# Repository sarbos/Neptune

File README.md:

#Neptune

Open source software and hardware for inexpensive Underwater ROV

device - all code on the ROV side of the project. Includes sensor drivers, motor drivers, HTTP communication, etc.

host - python host code to communicate with the device over http. Provides UI for controlling and viewing cameras and main board. Also interprets USB joystick and gamepad controls.

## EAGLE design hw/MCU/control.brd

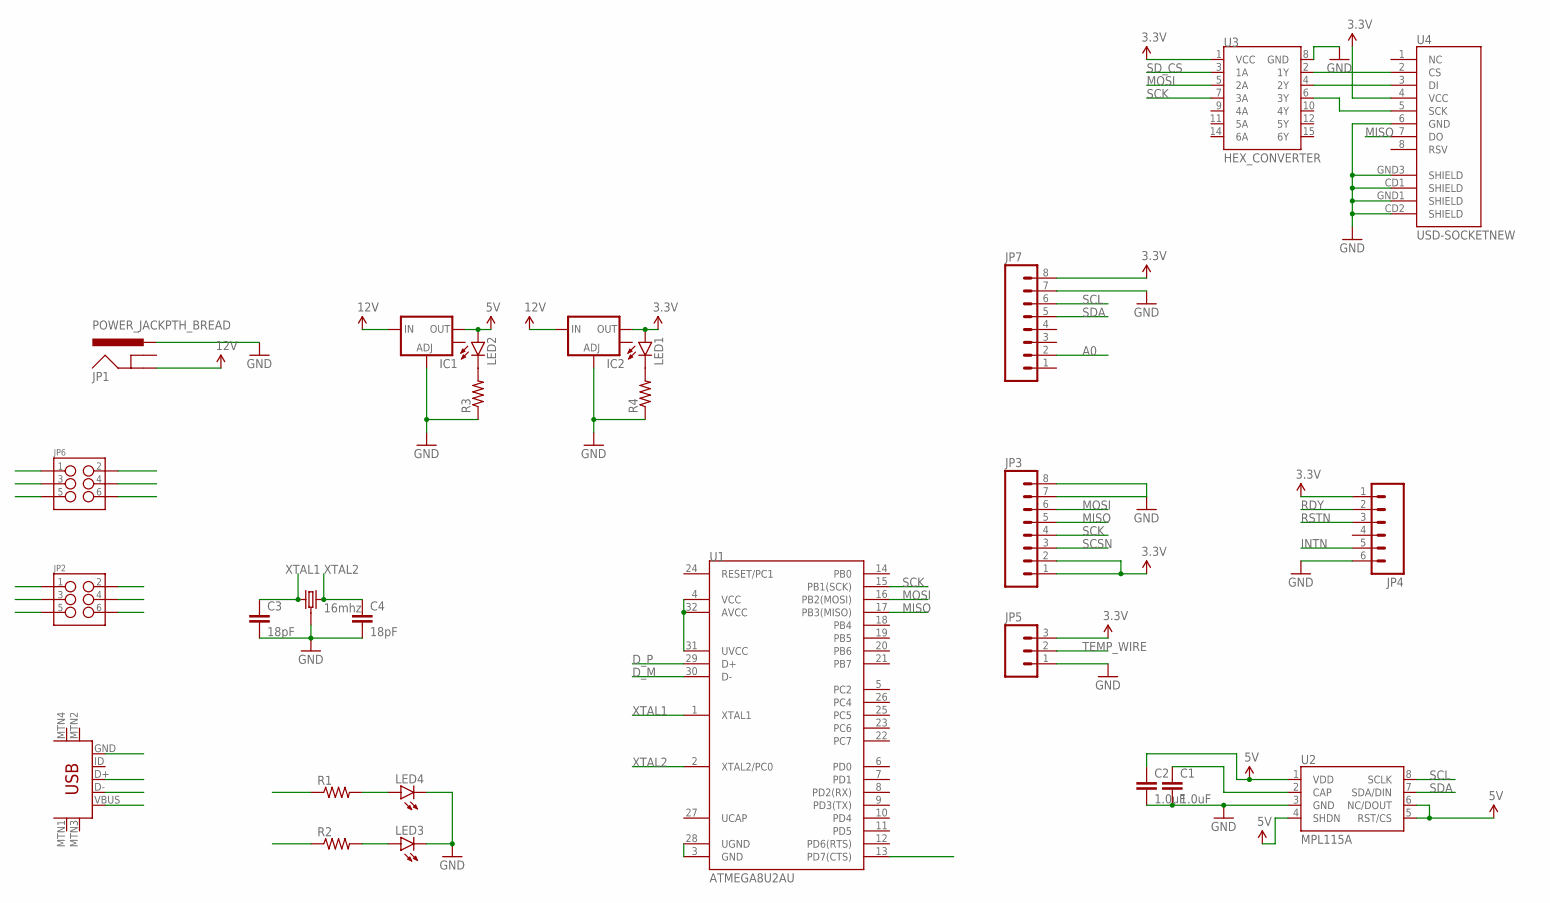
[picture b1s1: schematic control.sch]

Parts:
C1, C2: 1.0uF; 0603-CAP
C3, C4: 18pF; 0603-CAP
IC1, IC2: V_REG_LM1117SOT223; SOT223
JP1: POWER_JACKPTH_BREAD; POWER_JACK_PTH_BREAD
JP2, JP6: M03X2SHROUD; 2X3-SHROUDED
JP3, JP7: M08; 1X08_ROUND
JP4: M06SILK_FEMALE_PTH; 1X06
JP5: M03PTH; 1X03
LED1, LED2, LED3, LED4: LED0603; LED-0603
R1, R2, R3, R4: RESISTOR0603-RES; 0603-RES
U1: ATMEGA8U2AU; TQFP32-08
U2: MPL115A; LGA8
U3: HEX_CONVERTER; SO016
U4: USD-SOCKETNEW; MICRO-SD-SOCKET-PP
U$3: 16mhz; CRYSTAL-SMD-5X3
U$5: USB-MINIB-5PIN; USB-MINIB

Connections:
3.3V: IC2.2 (OUT), JP3.1, JP3.2, JP4.1, JP5.3, JP7.8, LED1.A, U3.1 (VCC), U4.4 (VCC)
5V: C2.1, IC1.2 (OUT), LED2.A, U2.1 (VDD), U2.4 (SHDN), U2.5 (RST/CS), U2.6 (NC/DOUT)
12V: IC1.3 (IN), IC2.3 (IN), JP1.GND
A0: JP7.2
D_M: U1.30 (D-)
D_P: U1.29 (D+)
GND: C1.2, C2.2, C3.2, C4.2, IC1.1 (ADJ), IC2.1 (ADJ), JP1.PWR, JP4.6, JP5.1, JP7.7, LED3.C, LED4.C, R3.1, R4.1, U2.3 (GND), U3.8 (GND), U4.6 (GND), U4.CD1 (SHIELD), U4.CD2 (SHIELD), U4.GND1 (SHIELD), U4.GND3 (SHIELD), U$3.2 (3), U$3.4 (3)
INTN: JP4.5
MISO: JP3.5, U1.17 (PB3(MISO)), U4.7 (DO)
MOSI: JP3.6, U1.16 (PB2(MOSI)), U3.5 (2A)
unnamed: JP3.7, JP3.8
unnamed: LED4.A, R1.2
unnamed: LED3.A, R2.2
unnamed: LED2.C, R3.2
unnamed: LED1.C, R4.2
unnamed: U3.2 (1Y), U4.2 (CS)
unnamed: U3.4 (2Y), U4.3 (DI)
unnamed: U3.6 (3Y), U4.5 (SCK)
unnamed: C1.1, U2.2 (CAP)
unnamed: U1.3 (GND), U1.28 (UGND)
unnamed: U1.4 (VCC), U1.31 (UVCC), U1.32 (AVCC)
RDY: JP4.2
RSTN: JP4.3
SCK: JP3.4, U1.15 (PB1(SCK)), U3.7 (3A)
SCL: JP7.6, U2.8 (SCLK)
SCSN: JP3.3
SDA: JP7.5, U2.7 (SDA/DIN)
SD_CS: U3.3 (1A)
TEMP_WIRE: JP5.2
XTAL1: C3.1, U1.1 (XTAL1), U$3.3 (1)
XTAL2: C4.1, U1.2 (XTAL2/PC0), U$3.1 (2)

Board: 2 copper layers, 27 parts (1 on the bottom side), 22 nets, no tracks yet.

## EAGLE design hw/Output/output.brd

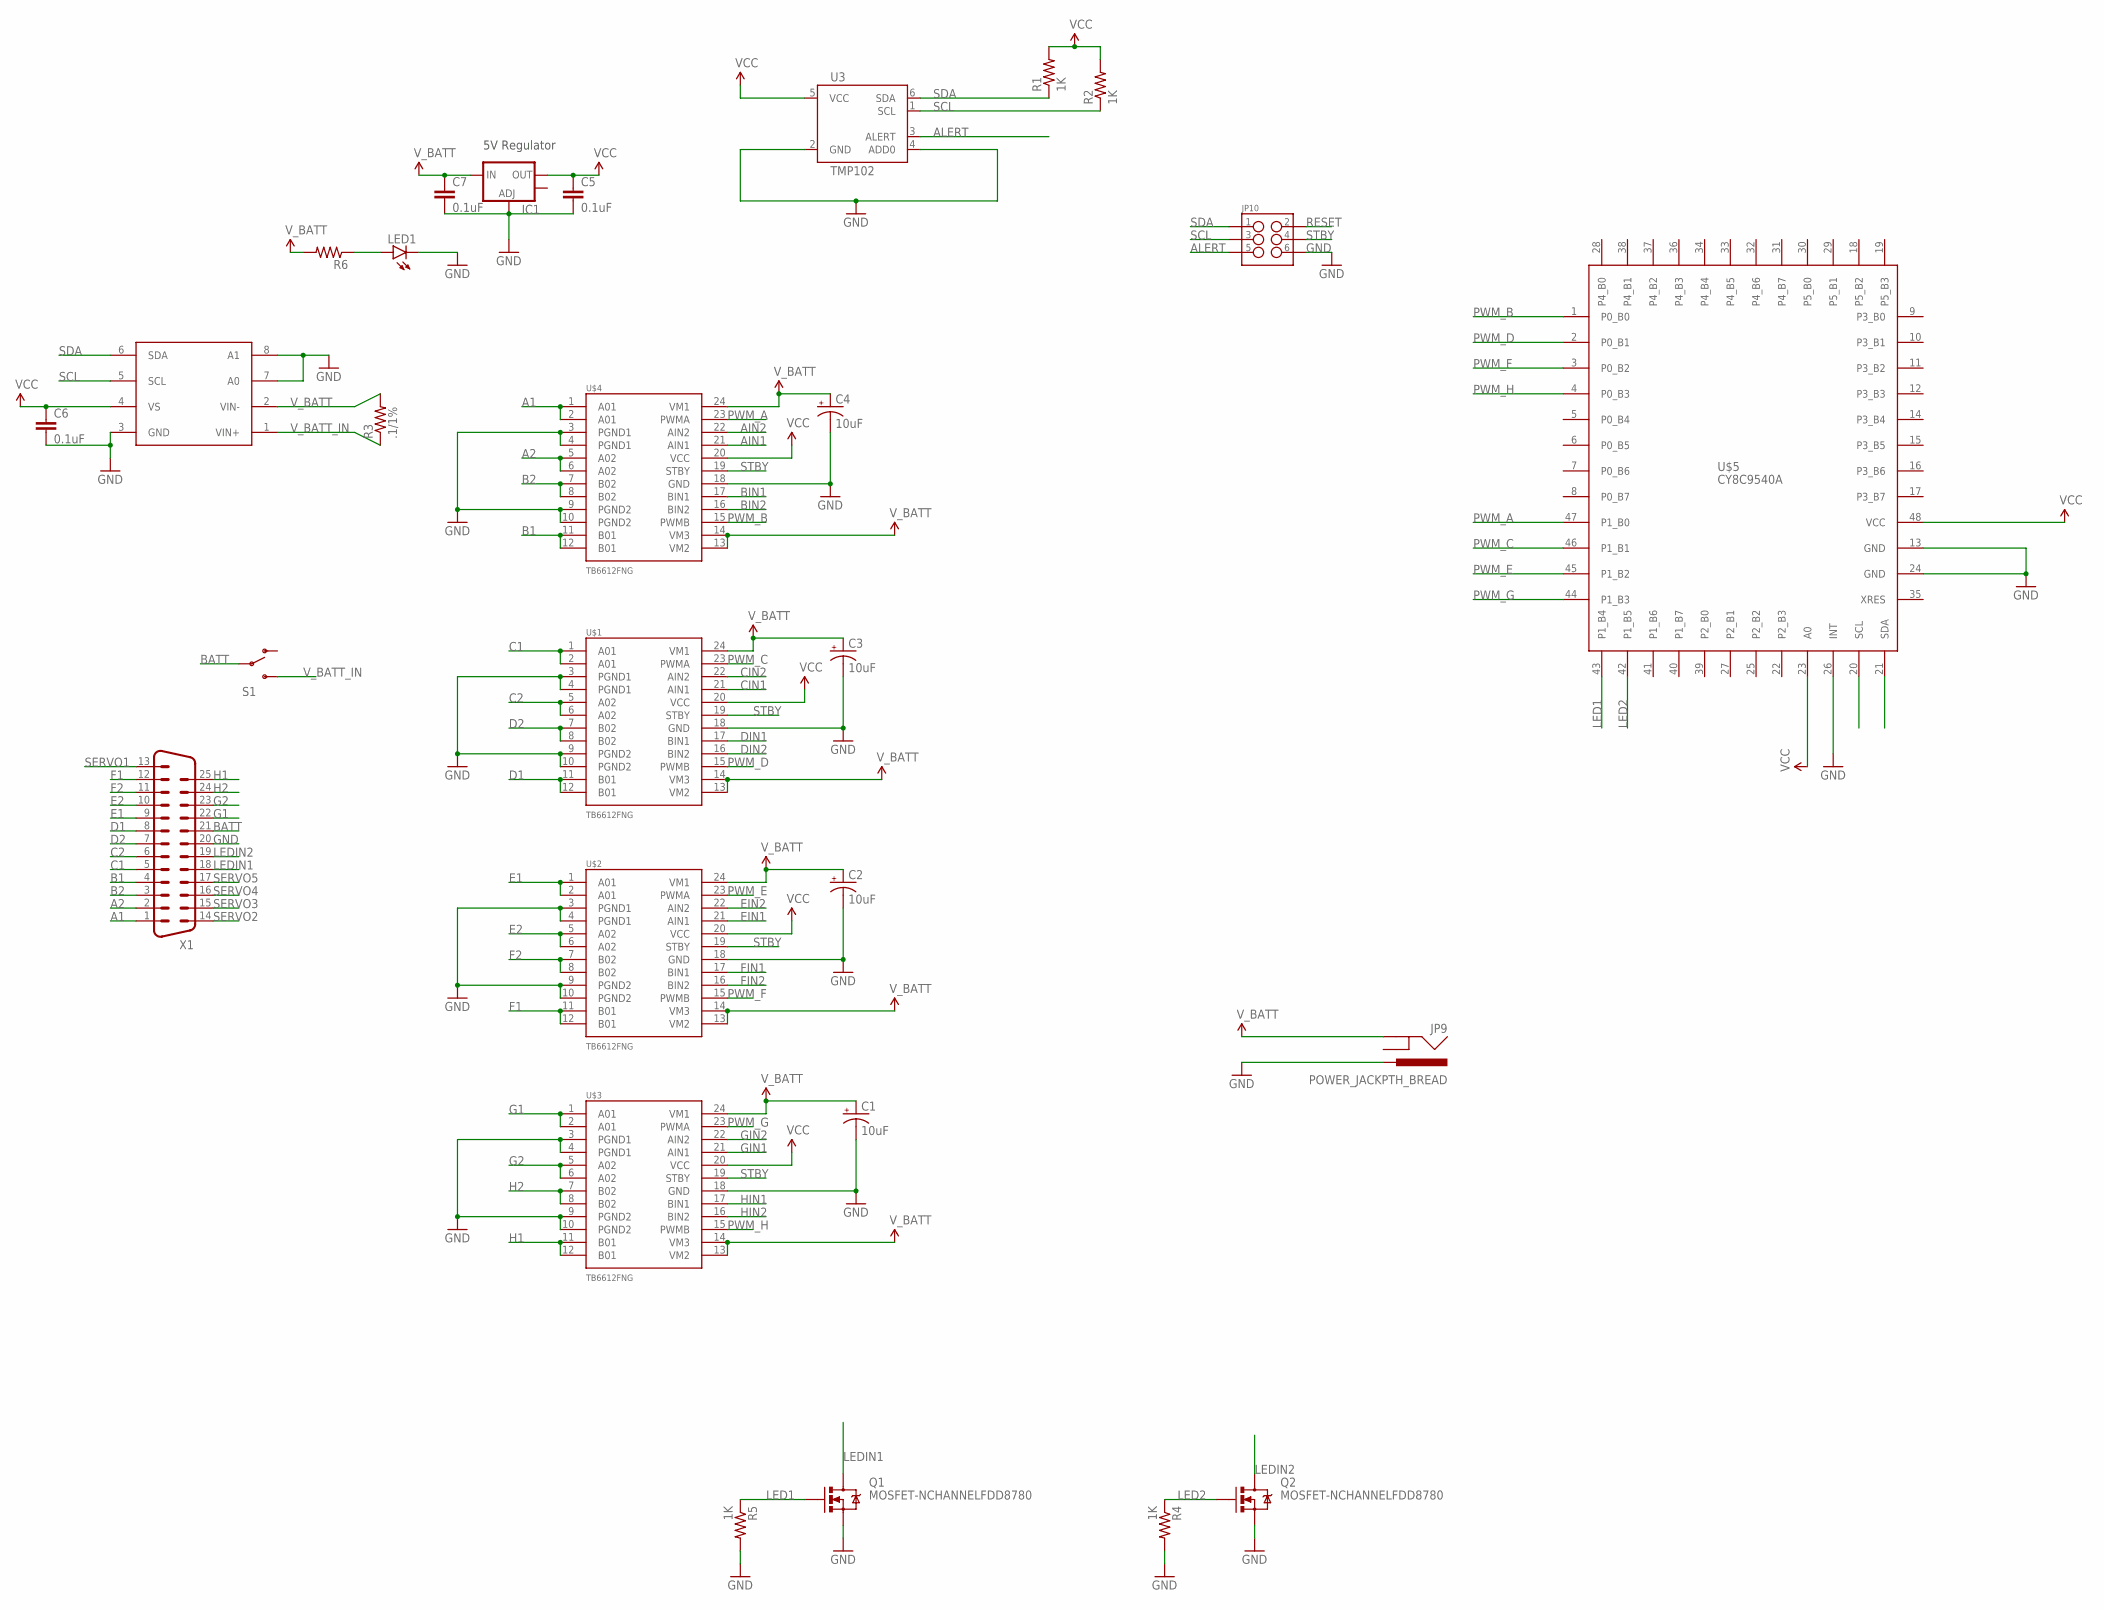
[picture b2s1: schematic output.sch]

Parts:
C1, C2, C3, C4: 10uF; EIA3528
C5, C6, C7: 0.1uF; 0603-CAP
IC1: V_REG_LM1117SOT223; SOT223
JP9: POWER_JACKPTH_BREAD; POWER_JACK_PTH_BREAD
JP10: M03X2SHROUD; 2X3-SHROUDED
LED1: LED0603; LED-0603
Q1, Q2: MOSFET-NCHANNELFDD8780; DPAK
R1, R2, R4, R5: 1K; 0603-RES
R3: .1/1%; R2512
R6: RESISTOR0603-RES; 0603-RES
S1: SWITCH-SPDTKIT; SWITCH-SPDT_KIT
U3: TMP102; SOT563
U$1, U$2, U$3, U$4: TB6612FNG; SSOP24
U$5: CY8C9540A; 48-SSOP-CY
U$6: INA219; SOT23-8
X1: DB25D; M25D

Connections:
A1: U$4.1 (A01), U$4.2 (A01), X1.1
A2: U$4.5 (A02), U$4.6 (A02), X1.2
AIN1: U$4.21 (AIN1)
AIN2: U$4.22 (AIN2)
ALERT: JP10.5, U3.3 (ALERT)
B1: U$4.11 (B01), U$4.12 (B01), X1.4
B2: U$4.7 (B02), U$4.8 (B02), X1.3
BATT: S1.2, X1.21
BIN1: U$4.17 (BIN1)
BIN2: U$4.16 (BIN2)
C1: U$1.1 (A01), U$1.2 (A01), X1.5
C2: U$1.5 (A02), U$1.6 (A02), X1.6
CIN1: U$1.21 (AIN1)
CIN2: U$1.22 (AIN2)
D1: U$1.11 (B01), U$1.12 (B01), X1.8
D2: U$1.7 (B02), U$1.8 (B02), X1.7
DIN1: U$1.17 (BIN1)
DIN2: U$1.16 (BIN2)
E1: U$2.1 (A01), U$2.2 (A01), X1.9
E2: U$2.5 (A02), U$2.6 (A02), X1.10
EIN1: U$2.21 (AIN1)
EIN2: U$2.22 (AIN2)
F1: U$2.11 (B01), U$2.12 (B01), X1.12
F2: U$2.7 (B02), U$2.8 (B02), X1.11
FIN1: U$2.17 (BIN1)
FIN2: U$2.16 (BIN2)
G1: U$3.1 (A01), U$3.2 (A01), X1.22
G2: U$3.5 (A02), U$3.6 (A02), X1.23
GIN1: U$3.21 (AIN1)
GIN2: U$3.22 (AIN2)
GND: C1.C (-), C2.C (-), C3.C (-), C4.C (-), C5.2, C6.2, C7.2, IC1.1 (ADJ), JP9.PWR, JP10.6, LED1.C, Q1.3 (S), Q2.3 (S), R4.2, R5.2, U3.2 (GND), U3.4 (ADD0), U$1.3 (PGND1), U$1.4 (PGND1), U$1.9 (PGND2), U$1.10 (PGND2), U$1.18 (GND), U$2.3 (PGND1), U$2.4 (PGND1), U$2.9 (PGND2), U$2.10 (PGND2), U$2.18 (GND), U$3.3 (PGND1), U$3.4 (PGND1), U$3.9 (PGND2), U$3.10 (PGND2), U$3.18 (GND), U$4.3 (PGND1), U$4.4 (PGND1), U$4.9 (PGND2), U$4.10 (PGND2), U$4.18 (GND), U$5.13 (GND), U$5.24 (GND), U$5.26 (INT), U$6.3 (GND), U$6.7 (A0), U$6.8 (A1), X1.20
H1: U$3.11 (B01), U$3.12 (B01), X1.25
H2: U$3.7 (B02), U$3.8 (B02), X1.24
HIN1: U$3.17 (BIN1)
HIN2: U$3.16 (BIN2)
LED1: Q1.1 (G), R5.1, U$5.43 (P1_B4)
LED2: Q2.1 (G), R4.1, U$5.42 (P1_B5)
LEDIN1: Q1.4 (D), X1.18
LEDIN2: Q2.4 (D), X1.19
unnamed: LED1.A, R6.1
PWM_A: U$4.23 (PWMA), U$5.47 (P1_B0)
PWM_B: U$4.15 (PWMB), U$5.1 (P0_B0)
PWM_C: U$1.23 (PWMA), U$5.46 (P1_B1)
PWM_D: U$1.15 (PWMB), U$5.2 (P0_B1)
PWM_E: U$2.23 (PWMA), U$5.45 (P1_B2)
PWM_F: U$2.15 (PWMB), U$5.3 (P0_B2)
PWM_G: U$3.23 (PWMA), U$5.44 (P1_B3)
PWM_H: U$3.15 (PWMB), U$5.4 (P0_B3)
RESET: JP10.2
SCL: JP10.3, R2.1, U3.1 (SCL), U$5.20 (SCL), U$6.5 (SCL)
SDA: JP10.1, R1.1, U3.6 (SDA), U$5.21 (SDA), U$6.6 (SDA)
SERVO1: X1.13
SERVO2: X1.14
SERVO3: X1.15
SERVO4: X1.16
SERVO5: X1.17
STBY: JP10.4, U$1.19 (STBY), U$2.19 (STBY), U$3.19 (STBY), U$4.19 (STBY)
VCC: C5.1, C6.1, IC1.2 (OUT), R1.2, R2.2, U3.5 (VCC), U$1.20 (VCC), U$2.20 (VCC), U$3.20 (VCC), U$4.20 (VCC), U$5.23 (A0), U$5.48 (VCC), U$6.4 (VS)
V_BATT: C1.A (+), C2.A (+), C3.A (+), C4.A (+), C7.1, IC1.3 (IN), JP9.GND, R3.2, R6.2, U$1.13 (VM2), U$1.14 (VM3), U$1.24 (VM1), U$2.13 (VM2), U$2.14 (VM3), U$2.24 (VM1), U$3.13 (VM2), U$3.14 (VM3), U$3.24 (VM1), U$4.13 (VM2), U$4.14 (VM3), U$4.24 (VM1), U$6.2 (VIN-)
V_BATT_IN: R3.1, S1.3 (S), U$6.1 (VIN+)

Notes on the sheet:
5V Regulator

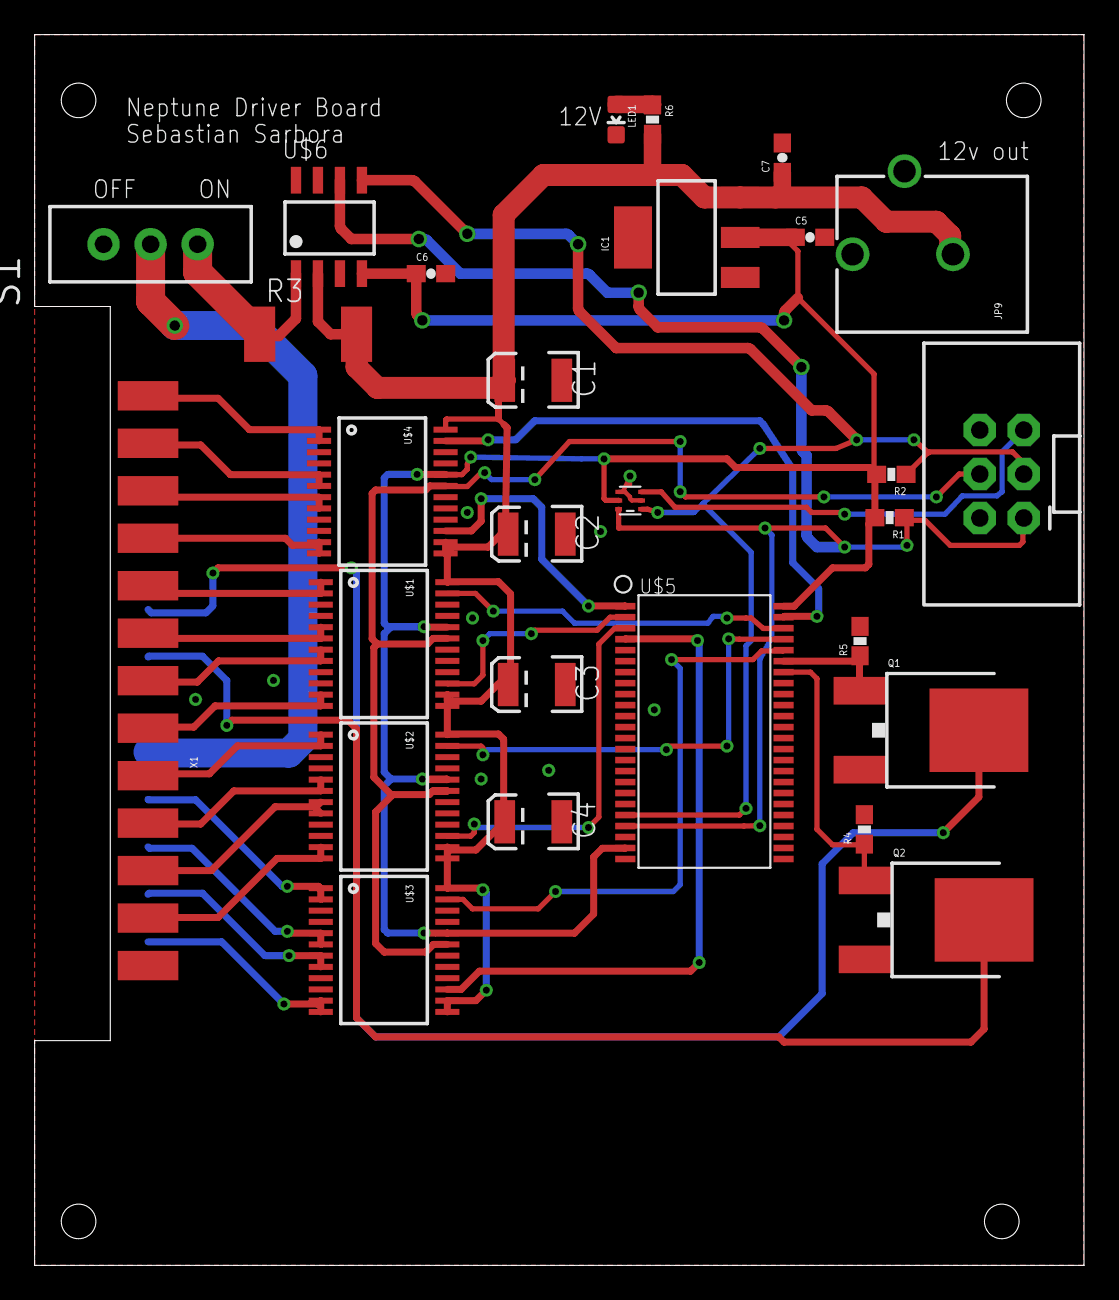
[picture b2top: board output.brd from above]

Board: 2 copper layers, 60.6 x 71.1 mm, 28 parts (0 on the bottom side), 38 nets.

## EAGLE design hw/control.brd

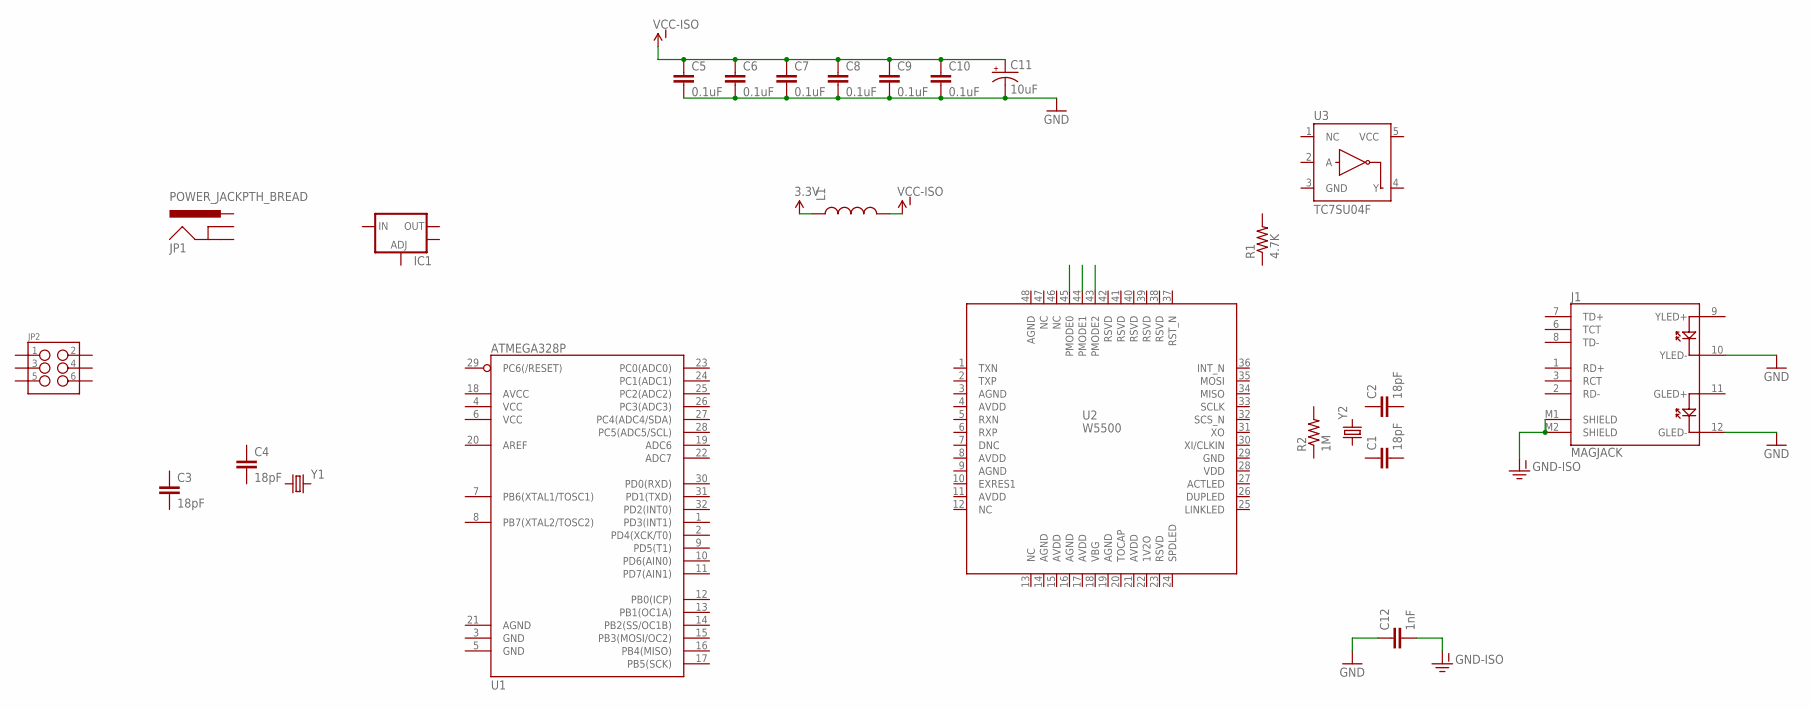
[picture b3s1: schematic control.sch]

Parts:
C1, C2, C3, C4: 18pF; 0603-CAP
C5, C6, C7, C8, C9, C10: 0.1uF; 0603-CAP
C11: 10uF; EIA3216
C12: 1nF; 0603-CAP
IC1: V_REG_LM1117SOT223; SOT223
J1: MAGJACK
JP1: POWER_JACKPTH_BREAD; POWER_JACK_PTH_BREAD
JP2: M03X2SHROUD; 2X3-SHROUDED
L1: INDUCTOR0603; 0603
R1: 4.7K; 0603-RES
R2: 1M; 0603-RES
U1: ATMEGA328P; TQFP32-08
U2: W5500
U3: TC7SU04F; SOT23-5
Y1, Y2: CRYSTALHC49US; HC49US

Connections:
3.3V: L1.1
GND: C5.2, C6.2, C7.2, C8.2, C9.2, C10.2, C11.C (-), C12.1, J1.10 (YLED-), J1.12 (GLED-)
GND-ISO: C12.2, J1.M1 (SHIELD), J1.M2 (SHIELD)
VCC-ISO: C5.1, C6.1, C7.1, C8.1, C9.1, C10.1, C11.A (+), L1.2

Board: 2 copper layers, 24 parts (0 on the bottom side), 3 nets, no tracks yet.

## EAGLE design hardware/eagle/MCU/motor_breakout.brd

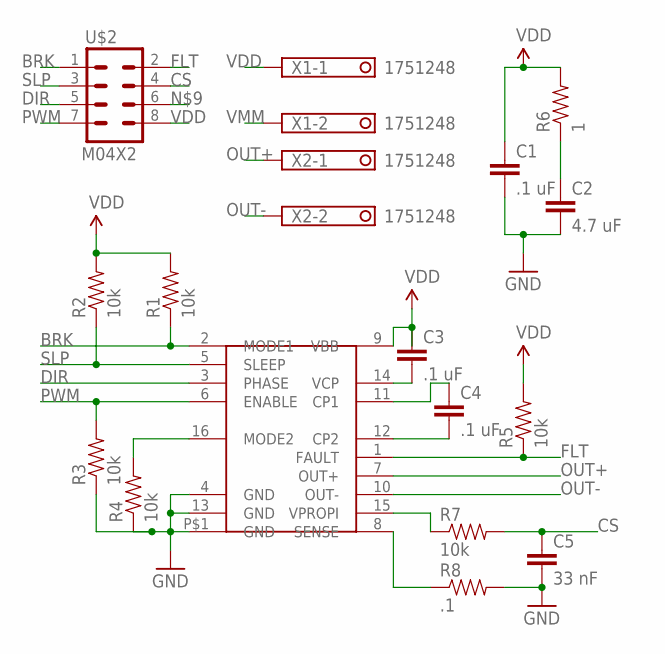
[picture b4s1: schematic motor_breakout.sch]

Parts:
C1, C3, C4: .1 uF; CAP-PTH-SMALL
C2: 4.7 uF; CAP-PTH-SMALL
C5: 33 nF; CAP-PTH-SMALL
R1, R2, R3, R4, R5, R7: 10k; 0603-RES
R6: 1; 0603-RES
R8: .1; 0603-RES
U$1: DRV8801PWP; TSSOP16
U$2: M04X2; 2X4
X1, X2: 1751248

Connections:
BRK: R1.1, U$1.2 (MODE1), U$2.1
CS: C5.1, R7.2, U$2.4
DIR: U$1.3 (PHASE), U$2.5
FLT: R5.1, U$1.1 (FAULT), U$2.2
GND: C1.2, C2.2, C5.2, R3.1, R4.1, R8.2, U$1.4 (GND), U$1.13 (GND), U$1.P$1 (GND)
unnamed: R4.2, U$1.16 (MODE2)
unnamed: R8.1, U$1.8 (SENSE)
unnamed: R7.1, U$1.15 (VPROPI)
unnamed: C3.2, U$1.14 (VCP)
unnamed: C4.1, U$1.11 (CP1)
unnamed: C4.2, U$1.12 (CP2)
unnamed: C2.1, R6.1
OUT+: U$1.7 (OUT+), X2.1
OUT-: U$1.10 (OUT-), X2.2
PWM: R3.2, U$1.6 (ENABLE), U$2.7
SLP: R2.1, U$1.5 (SLEEP), U$2.3
VDD: C1.1, C3.1, R1.2, R2.2, R5.2, R6.2, U$1.9 (VBB), U$2.8, X1.1
VMM: X1.2

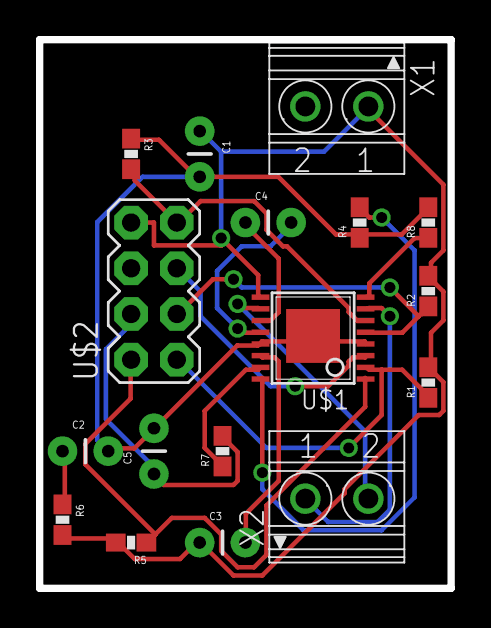
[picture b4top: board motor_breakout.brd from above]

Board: 2 copper layers, 22.9 x 30.5 mm, 17 parts (0 on the bottom side), 17 nets.

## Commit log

2014-09-20 got streaming mjpeg viewer working. Needs some enhancements to imporve image quality and to lower latency.
2014-09-21 joystick reading
2014-12-04 started application interface
2014-12-04 added space for video feed
2014-12-04 Added directional controls
2014-12-10 created motor controller library, set up arduino tools for use with make, moved directory structure for organization, added folder for ENCBoot, which will be the default bootloader
2014-12-15 Updated readme to reflect semester changes
2014-12-21 finished makefile for building arduino core library
2014-12-22 modified makefiles to better reflect project structure. Added header for ethernet module.Added gitignore to ignore build files
2014-12-28 added ethercard enc28j60 driver, and created ipv4 and udp classes with minimal and untested functionality.
2015-02-08 added documentation folder
2015-02-16 empty django project
2015-02-24 Start of django project. Rough site template with places to add dynamic content such as webcam stream
2015-02-28 Added simple Neptune protocol headers. Implementation to come soon.
2015-02-28 Made some more minor naming changes, and fixed compiler warnings and bugs.
2015-02-28 fixed the filepath so templates will work outside of local directory
2015-02-28 fixed camera code to work on 2.7
2015-02-28 initial hardware library
2015-02-28 Added TI TSSOP16, need to edit for power pad.
2015-02-28 Moved diagram
2015-02-28 generates values for raw motor data and position motor data. Will be used for testing without an actual device
2015-02-28 wrote constructor, serialize and deserialize functions
2015-02-28 Eagle schematic for accelerometer taken from https://github.com/adafruit/Adafruit-LSM303-PCB
2015-02-28 tested constructor
2015-03-04 added comments to the main code loop to lay out the gameplan.
2015-03-06 Modified build system to work with travis-ci
2015-03-07 adding wiznet
2015-03-07 testing arduino install
2015-03-07 doing a raw download of arduino 1.6.0 and installing in place
2015-03-07 small syntax error with unzipping
2015-03-07 Removed arduino and libraries from the repo, now build from the arduino install
2015-03-07 added some indiredction for building lib-core. Working on libraries next.
2015-03-07 forgot to add make all
2015-03-08 Created MCU breakout board and schematic
2015-03-09 removed the arduino main file from the core library to replace with user's main
2015-03-15 added ground pour and power connection to MCU breakout
2015-04-21 started breakout board connecting arduino pins to components
2015-05-05 All components added to PCB schematic: Arduino, ethernet, 6 MCUs, GPIO expander, PWM expander
2015-09-22 Add ethernet library and MIT license
2015-12-04 add onewire library for temp sensor usage. removed servo_test
2015-12-04 added function to pull temperature sensor data and convert to meaningful data in celcius
2015-12-04 fixed makefile and include structure to no longer break the build
2015-12-04 added wiring reverence to get rid of more travis build issues
2015-12-04 actual fix for wiring include. delayMicroseconds should not be undefined now
2015-12-04 added hooks reference to access yield function
2015-12-05 Fixed makefile to build a programmable intel-32 hex file as opposed to an elf-32 object file
2015-12-05 fixed button locations, added camera toggle
2016-01-05 cleaned up repo.
2016-04-15 Updated main host file to read from actual neptune camera instead of dummy camera. wrote test python application to send packets that activate motors.
2016-04-15 Added arduino files for network communication. Added arduino file for driver co-processor
2016-04-15 Added eagle design files
2016-09-21 Consolidated output board to use single control IC (CY8C9540A), removed servo pwm lines for this revision.
2016-09-21 Added power indication LED and Battery current/voltage measurement to output board. Added atmega32u2, IMU header, Temp sensor connector, and wiz55io header to control board.
2016-09-21 Added Power Switch to output board.
2016-09-28 Laid out positions of components on board.
2017-06-14 Massive change. Dropped all arduino support, moved to LUFA. Removed all hardware files and will move them to a seperate repo.
    Ported WizNet library to the atmega32u4. Got basic sockets, both TCP and UDP working.

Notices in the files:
parts and their libraries:
SparkFun-Capacitors: Licensing: Creative Commons ShareAlike 4.0 International - https://creativecommons.org/licenses/by-sa/4.0
